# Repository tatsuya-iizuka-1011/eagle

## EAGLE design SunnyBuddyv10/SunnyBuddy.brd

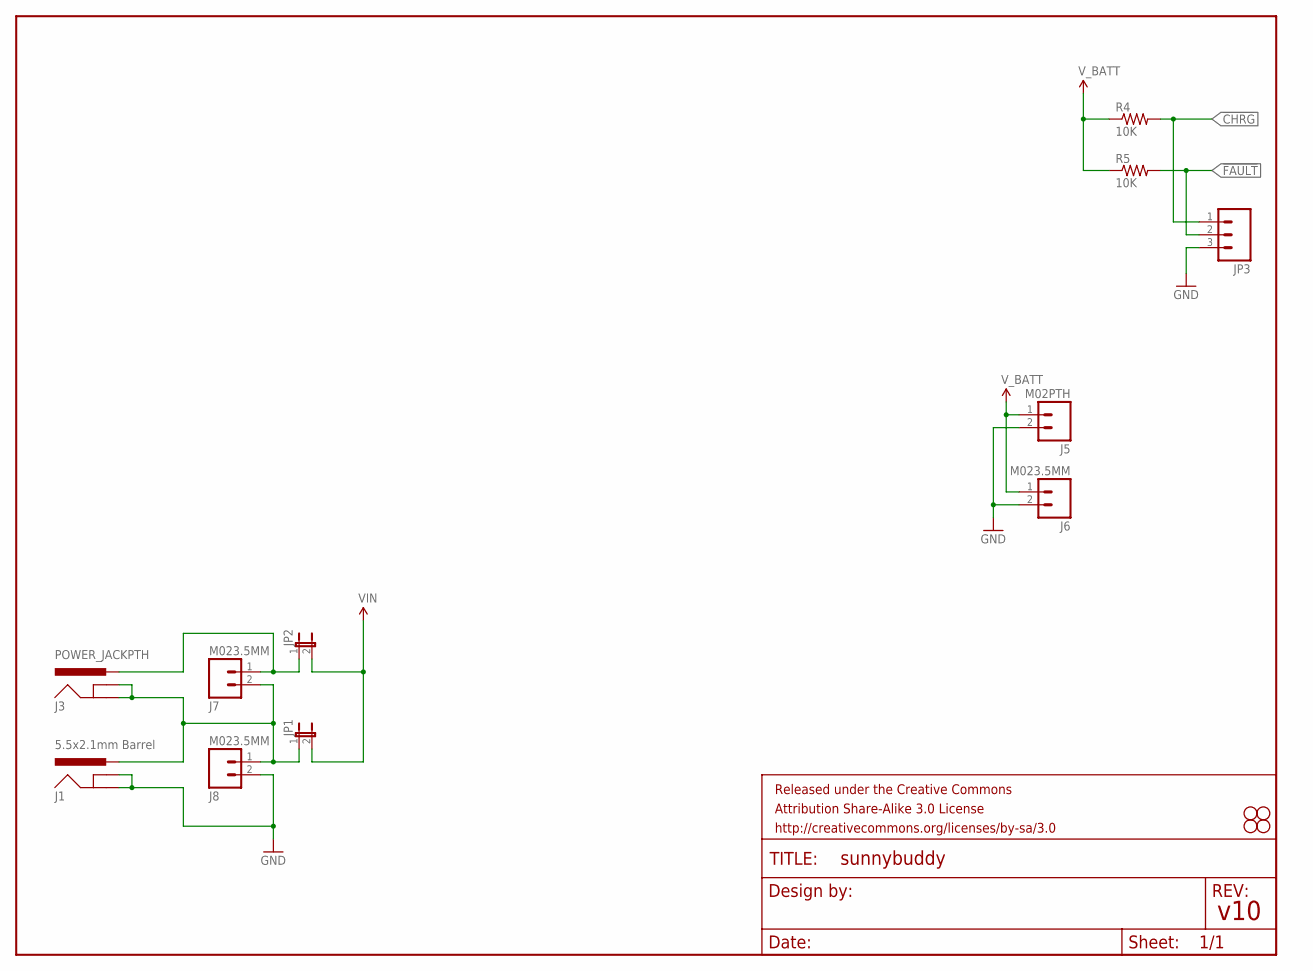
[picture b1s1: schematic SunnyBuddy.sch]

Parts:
FRAME1: FRAME-LETTER; CREATIVE_COMMONS
J1: 5.5x2.1mm Barrel; POWER_JACK_SMD
J3: POWER_JACKPTH; POWER_JACK_PTH
J5: M02PTH; 1X02
J6, J7, J8: M023.5MM; SCREWTERMINAL-3.5MM-2
JP1: JUMPER-2SMD-NC; SJ_2S
JP2: JUMPER-2SMD-NO; SJ_2S-NO
JP3: M03PTH; 1X03
R4, R5: 10K; 0603-RES
STANDOFF1, STANDOFF2, STANDOFF3, STANDOFF4: STAND-OFF

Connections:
!CHRG: JP3.1, R4.2
!FAULT: JP3.2, R5.2
GND: J1.GND (GNDBREAK), J1.P$4 (GND), J5.2, J6.2, J8.2, JP3.3
unnamed: J1.VIN0 (PWR), J3.GND, J3.GNDBREAK, J7.2, J8.1, JP1.1
SFSASDF: J3.PWR, J7.1, JP2.1
VIN: JP1.2, JP2.2
V_BATT: J5.1, J6.1, R4.1, R5.1

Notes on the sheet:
v10

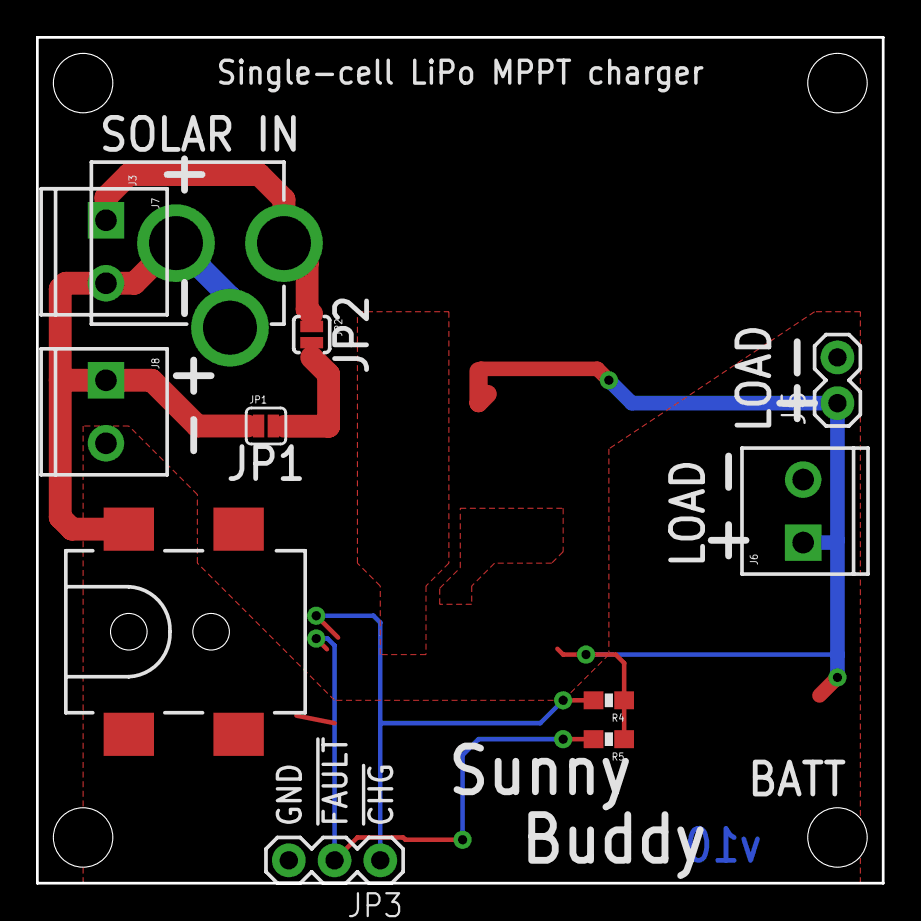
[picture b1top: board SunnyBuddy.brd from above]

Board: 2 copper layers, 47.0 x 47.0 mm, 16 parts (0 on the bottom side), 7 nets.

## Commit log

2015-12-15 first commit on Eagle
2016-01-27 sunny

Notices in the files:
parts and their libraries:
SparkFun-Aesthetics: Licensing: CC v3.0 Share-Alike You are welcome to use this library for commercial purposes.
SparkFun-Aesthetics: Released under the Creative Commons Attribution Share-Alike 3.0 License
SparkFun-Aesthetics: http://creativecommons.org/licenses/by-sa/3.0
